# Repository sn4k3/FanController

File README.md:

# FanController
 PWM fan controller using ATtiny85

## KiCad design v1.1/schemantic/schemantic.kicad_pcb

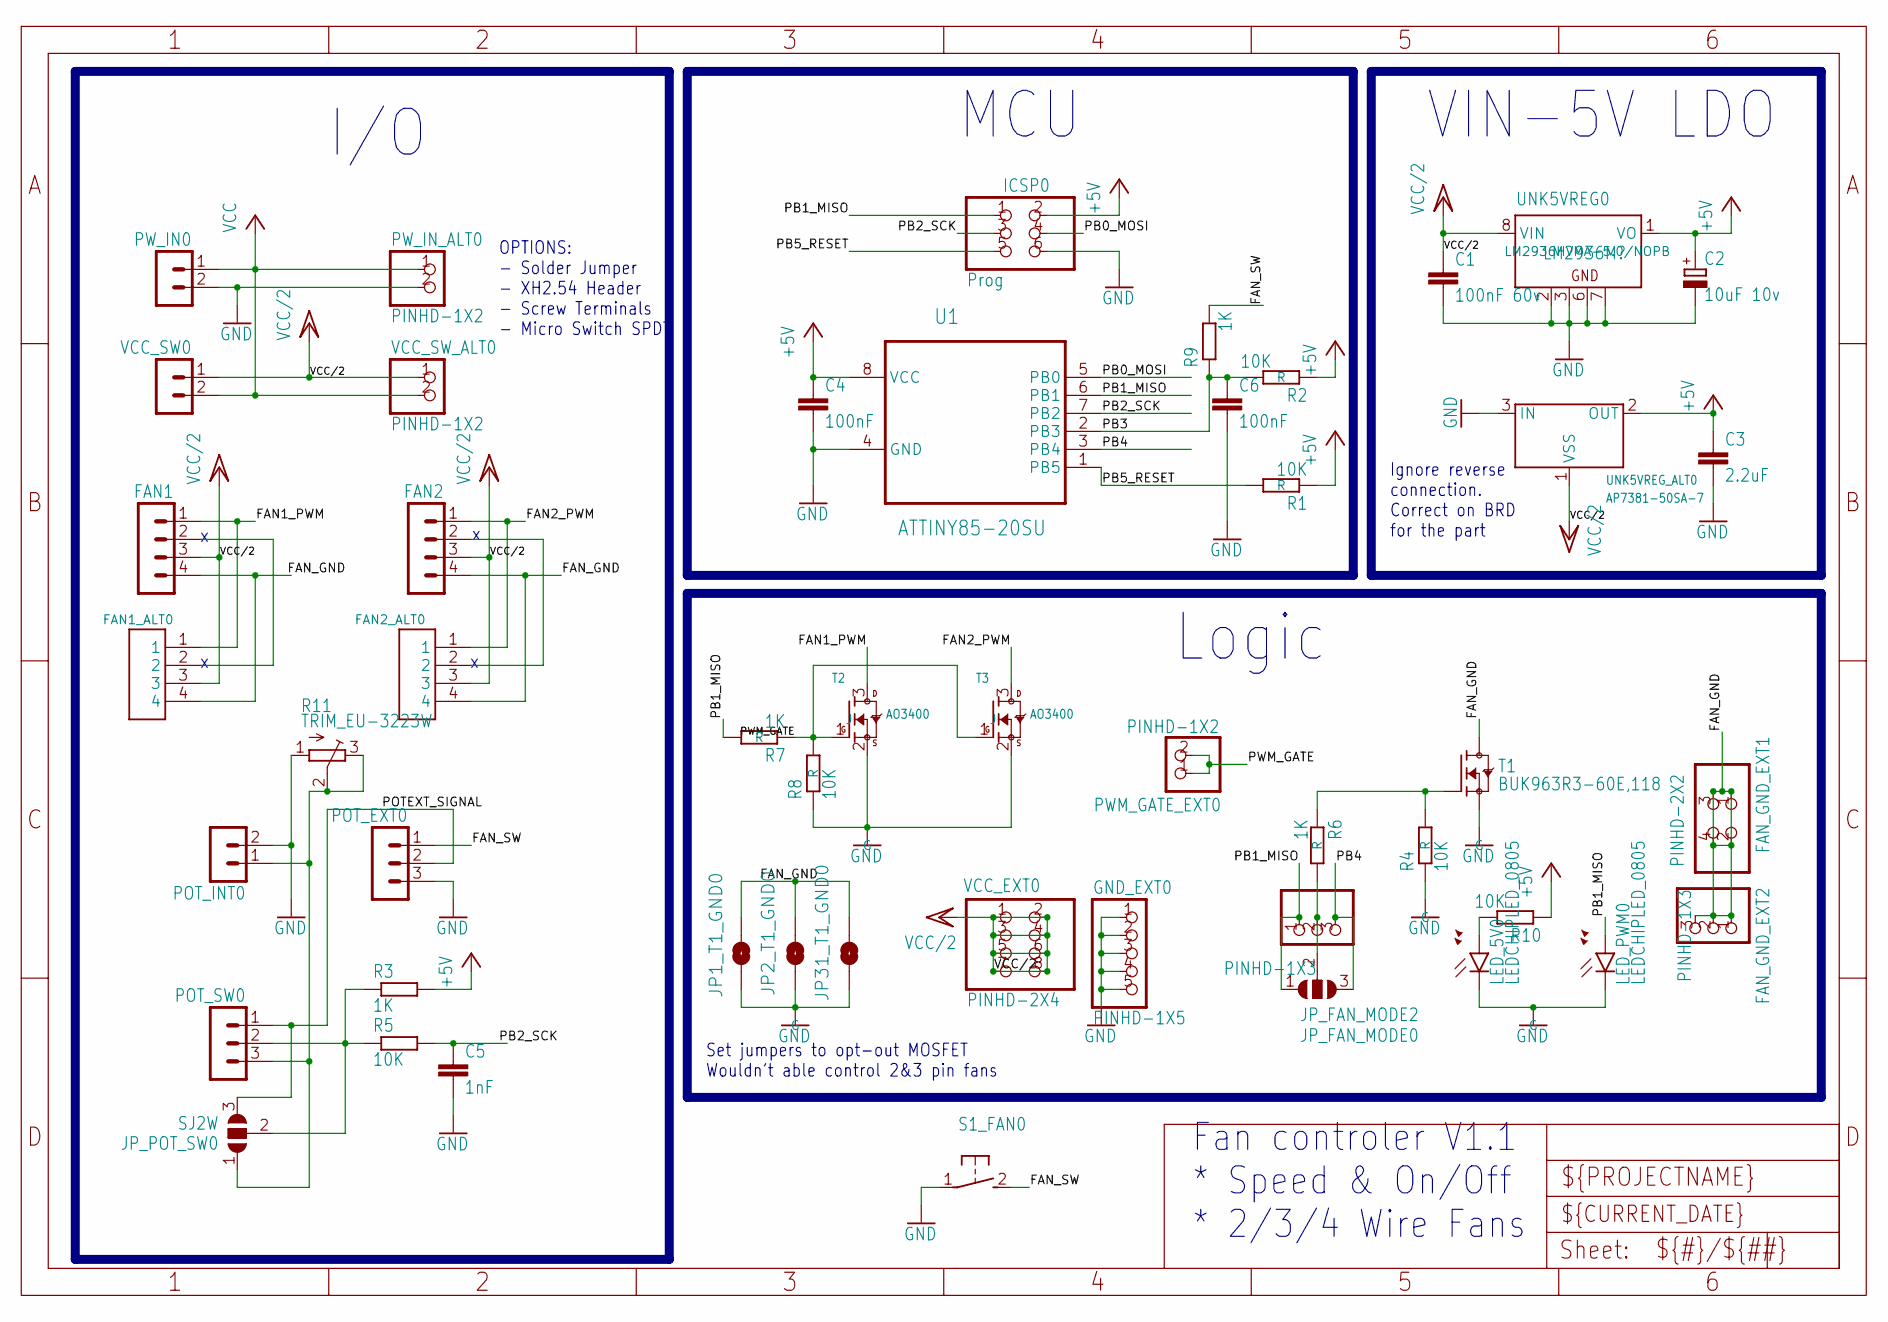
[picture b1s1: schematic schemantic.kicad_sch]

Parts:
C1: 100nF 60v; C1206
C2: 10uF 10v; SMC_E
C3: 2.2uF; C0805
C4, C6: 100nF; C0805
C5: 1nF; C0805
FAN1, FAN2: FAN1; B4P-VH
FAN1_ALT0, FAN2_ALT0: 1X4-BIG; 1X04-BIG
FAN_GND_EXT1: PINHD-2X2; 2X02
FAN_GND_EXT2: PINHD-1X3; 1X03
GND_EXT0: PINHD-1X5; 1X05
ICSP0: Prog; 2X03
JP1_T1_GND0, JP2_T1_GND0, JP31_T1_GND0: JUMPER-SMT_2_NO_NO-SILK; SMT-JUMPER_2_NO_NO-SILK
JP_FAN_MODE0: DC_COM_PWM; SJ_2
JP_FAN_MODE2: PINHD-1X3; 1X03
JP_POT_SW0: SJ2W; SJ_2
LED_5V0: LEDCHIPLED_0805; CHIPLED_0805
LED_PWM0: LEDCHIPLED_0805; CHIPLED_0805
POT_EXT0: POT_EXT; B3B-XH-A
POT_INT0: POT_INT; B2B-XH-A
POT_SW0: POT_SW; B3B-XH-A
PWM_GATE_EXT0: PINHD-1X2; 1X02
PW_IN0: Power In; B2P-VH
PW_IN_ALT0: PINHD-1X2; 1X02
R1, R2, R4, R5, R8, R10: 10K; R0805
R3, R6, R7, R9: 1K; R0805
R11: TRIM_EU-3223W; 3223W
S1_FAN0: DTSM-3
T1: BUK963R3-60E,118; D2PAK_TO263
T2, T3: AO3400; SOT23
U1: ATTINY85-20SU; SOIC127P798X216-8N
UNK5VREG0: LM2936M?; SO08; MPN LM2936HVMA-5.0/NOPB
UNK5VREG_ALT0: AP7381-50SA-7; XC6206_SOT-23
VCC_EXT0: PINHD-2X4; 2X04
VCC_SW0: Power SW; B2P-VH
VCC_SW_ALT0: PINHD-1X2; 1X02

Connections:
+5V: C2.+, C3.1, C4.1, ICSP0.2, R1.1, R2.1, R3.2, R10.1, U1.8 (VCC), UNK5VREG0.1 (VO), UNK5VREG_ALT0.2 (OUT)
FAN1_LATCH: FAN1.2, FAN1_ALT0.2
FAN1_PWM: FAN1.1, FAN1_ALT0.1, T2.3 (D)
FAN2_LATCH: FAN2.2, FAN2_ALT0.2
FAN2_PWM: FAN2.1, FAN2_ALT0.1, T3.3 (D)
FAN_GND: FAN1.4, FAN1_ALT0.4, FAN2.4, FAN2_ALT0.4, FAN_GND_EXT1.1, FAN_GND_EXT1.2, FAN_GND_EXT1.3, FAN_GND_EXT1.4, FAN_GND_EXT2.1, FAN_GND_EXT2.2, FAN_GND_EXT2.3, JP1_T1_GND0.2, JP2_T1_GND0.2, JP31_T1_GND0.2, T1.2 (D)
FAN_SW: POT_EXT0.1, R9.2, S1_FAN0.2
GND: C1.2, C2.-, C3.2, C4.2, C5.2, C6.2, GND_EXT0.1, GND_EXT0.2, GND_EXT0.3, GND_EXT0.4, GND_EXT0.5, ICSP0.6, JP1_T1_GND0.1, JP2_T1_GND0.1, JP31_T1_GND0.1, LED_5V0.C, LED_PWM0.C, POT_EXT0.3, POT_INT0.2, PW_IN0.2, PW_IN_ALT0.2, R4.1, R8.1, R11.1 (A), S1_FAN0.1, T1.3 (S), T2.2 (S), T3.2 (S), U1.4 (GND), UNK5VREG0.2 (GND@1), UNK5VREG0.3 (GND@2), UNK5VREG0.6 (GND@3), UNK5VREG0.7 (GND@4), UNK5VREG_ALT0.3 (IN)
JP1_COM: JP_FAN_MODE0.2, JP_FAN_MODE2.2, R6.2
LED1_ANODE: LED_5V0.A, R10.2
PB0_MOSI: ICSP0.4, U1.5 (PB0)
PB1_MISO: ICSP0.1, JP_FAN_MODE0.1, JP_FAN_MODE2.1, LED_PWM0.A, R7.2, U1.6 (PB1)
PB2_SCK: C5.1, ICSP0.3, R5.2, U1.7 (PB2)
PB3: C6.1, R2.2, R9.1, U1.2 (PB3)
PB4: JP_FAN_MODE0.3, JP_FAN_MODE2.3, U1.3 (PB4)
PB5_RESET: ICSP0.5, R1.2, U1.1 (PB5)
POTEXT_SIGNAL: JP_POT_SW0.3, POT_EXT0.2, POT_SW0.1
POTINT_SIGNAL: JP_POT_SW0.1, POT_INT0.1, POT_SW0.3, R11.2 (S), R11.3 (E)
POTSW_COM: JP_POT_SW0.2, POT_SW0.2, R3.1, R5.1
PWM_GATE: PWM_GATE_EXT0.1, PWM_GATE_EXT0.2, R7.1, R8.2, T2.1 (G), T3.1 (G)
T1_GATE: R4.2, R6.1, T1.1 (G)
VCC: PW_IN0.1, PW_IN_ALT0.1, VCC_SW0.2, VCC_SW_ALT0.2
VCC/2: C1.1, FAN1.3, FAN1_ALT0.3, FAN2.3, FAN2_ALT0.3, UNK5VREG0.8 (VIN), UNK5VREG_ALT0.1 (VSS), VCC_EXT0.1, VCC_EXT0.2, VCC_EXT0.3, VCC_EXT0.4, VCC_EXT0.5, VCC_EXT0.6, VCC_EXT0.7, VCC_EXT0.8, VCC_SW0.1, VCC_SW_ALT0.1

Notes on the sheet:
I/O
Fan controler V1.1 * Speed & On/Off * 2/3/4 Wire Fans
Logic
Set jumpers to opt-out MOSFET Wouldn't able control 2&3 pin fans
Ignore reverse connection. Correct on BRD for the part
OPTIONS: - Solder Jumper - XH2.54 Header - Screw Terminals - Micro Switch SPDT
MCU
VIN-5V LDO

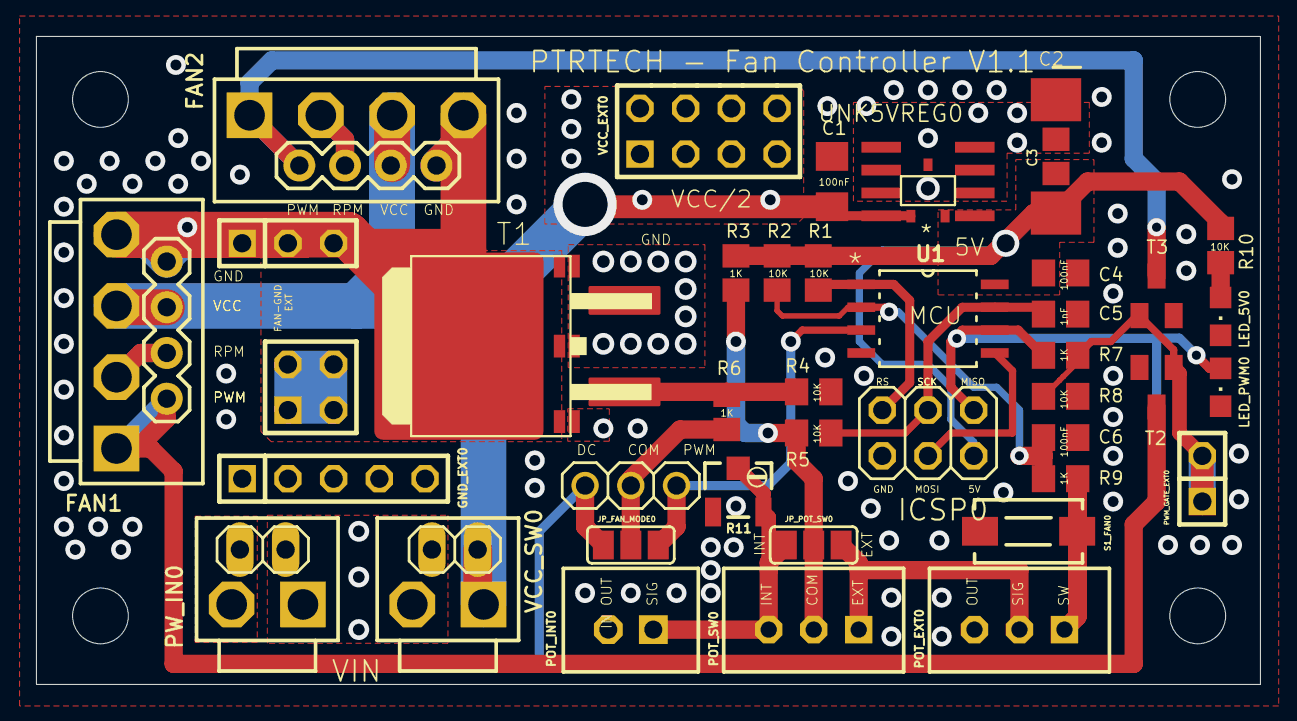
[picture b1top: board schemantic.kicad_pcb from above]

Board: 2 copper layers, 68.0 x 36.0 mm, 53 parts (0 on the bottom side), 23 nets.

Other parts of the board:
UNK_HOLE_0: dummyfp0
UNK_HOLE_1: dummyfp1
UNK_HOLE_2: dummyfp2
UNK_HOLE_3: dummyfp3

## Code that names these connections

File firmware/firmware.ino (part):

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 *
 *                       ATtiny25/45/85
 *                      -------u-------
 *  RST - A0 - (D 5) --| 1 PB5   VCC 8 |-- +5V
 *                     |               |
 * SWITCH A3 - (D 3) --| 2 PB3   PB2 7 |-- (D 2) - A1  --> 10K Potentiometer
 *                     |               |
 * MOSFET A2 - (D 4) --| 3 PB4   PB1 6 |-- (D 1) - PWM --> FET -> Fan PWM Wire
 *                     |               |
 *              Gnd ---| 4 GND   PB0 5 |-- (D 0) - PWM --> Disabled
 *                     -----------------
 *  https://thewanderingengineer.com/2014/08/11/pin-change-interrupts-on-attiny85/
 *
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
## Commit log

2025-07-31 Organize, add kicad convertion and fuse docs
